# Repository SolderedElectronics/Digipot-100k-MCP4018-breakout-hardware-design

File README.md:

# Digipot 100k MCP4018 breakout Hardware Design

## About the Product

|  |
| :----------------------------------------------------------: |
| [Buy Digipot 100k MCP4018 breakout](https://www.solde.red/333093) |

A digital potentiometer is a device identical to a potentiometer, except that instead of a physical rotating part that adjusts the resistance, it uses digital communication. Namely, the resistance of the digital potentiometer is adjusted via I2C communication.

Our module is based on the MCP4018 IC which has a total of 128 steps between 0 and 100k resistance values. This would mean that it is capable of doing resistance steps of approximately 781 ohms. It is controlled via I2C which makes it extremely easy to use.

---

## Repository Contents

This repository contains all design files for Digipot 100k MCP4018 breakout, organized as follows:

- **`CAD` folder**: Contains KiCAD design files, including:
  - Schematics
  - PCB layout
  - Panel PCB layout
  - Source 3D files in Fusion360, if any
  - All files are sorted by version with a detailed change log.
- **`OUTPUTS` folder**: Includes all production-ready files, such as:
  - Bill of Materials (BOM) and interactive BOM (iBOM)
  - PDF versions of schematics
  - 3D `.step` file of the board
  - 3D-printable models
  - Gerber files for PCB manufacturing
  - Image of the pinout of the board
  - Product image
  - Compliance, legal and generic sales documents

Refer to the `Change Log` in the CAD folder for details about updates between versions.

---

## Learn More About the Product

Beyond the repository, explore the following resources:

### Soldered Verify

The **Soldered Verify** system ensures every board you purchase from Soldered is fully functional. It also provides access to exclusive test data for your product. To get started, find the unique Soldered Verify ID on your product's packaging and enter the ID on the [Soldered Verify page](https://soldered.com/verify/) to access test results and additional product details.

### Soldered Community

Soldered Community is your go-to place for technical support. Our engineers track and answer all questions posted there, and it’s a great space for the maker community. Get answers to your questions and solutions for your challenges at [Soldered Community](https://soldered.com/community).

### solde.red

solde.red is an ultimate URL shortener and information hub. Access it by typing solde.red/ followed by your product SKU, e.g., [solde.red/333000](https://solde.red/333000), to find getting-started guides, datasheets, open-source hardware and software files, certifications, images, pinouts, and more. Read more about the shortener [here](https://solde.red/info/).

---

## Contributing

Contributions are welcome! Here’s how you can get involved:

- Submit pull requests to enhance the design or fix issues.
- Report bugs or problems by opening an issue.

We encourage community collaboration to make this product even better.

---

## About Soldered

[Soldered for Makers](https://soldered.com) specializes in designing and manufacturing electronic products tailored for enthusiasts, ranging from hobbyists to professionals. Our portfolio includes electronic boards, sensors, and actuators that are widely utilized in fields such as microelectronics, mechatronics, robotics, programming, and IoT. Every product we offer is designed in-house and built upon open-source hardware and software platforms. Proudly certified and manufactured within the European Union, our catalog likely includes the product you need for your project.

We complement these products with comprehensive tutorials and manuals, product descriptions, schematics, programming codes, and project examples. Our round-the-clock [customer and technical support](https://soldered.com/community) is available for all our products, irrespective of the sales channel. Soldered’s success and services reflect our maker community’s unwavering [trust](https://www.trustpilot.com/review/soldered.com), for which we are deeply grateful. Join our community and create using Soldered products.

---

## License

All Soldered open-source hardware (OSH) is under The TAPR Open Hardware License. Read more in the LICENSE file located in this repository.

**Disclaimer:**

No warranty - all designs in this repository are distributed in the hope that they will be useful, but without any warranty. They are provided "AS IS", therefore without warranty of any kind, either expressed or implied. The entire quality and performance of what you do with the contents of this repository are your responsibility. In no event Soldered Electronics will be liable for your damages, or losses, including any general, special, incidental, or consequential damage arising out of the use or inability to use the contents of this repository. 

---

## Have fun!

Thank you for your support from your fellow makers at Soldered Electronics.

Happy Making!

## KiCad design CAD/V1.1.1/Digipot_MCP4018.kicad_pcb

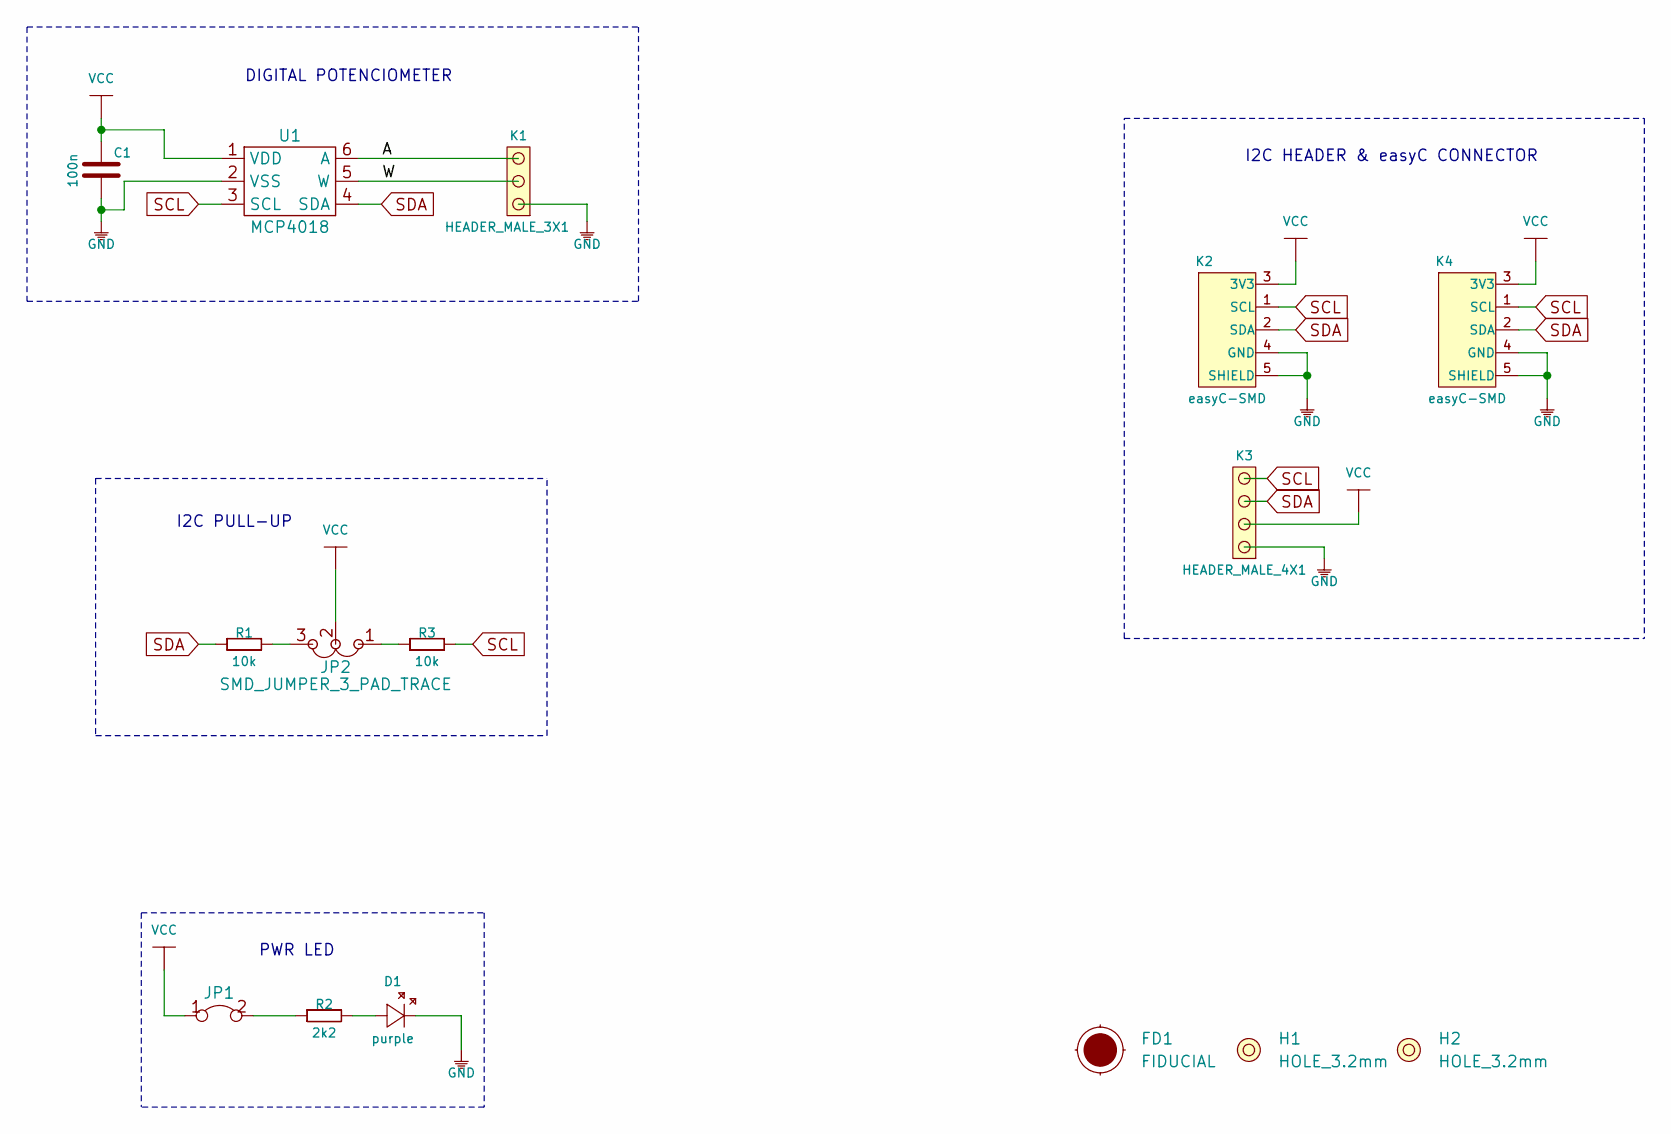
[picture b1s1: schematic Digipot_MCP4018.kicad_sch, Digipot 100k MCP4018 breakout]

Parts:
C1: 100n; 0603C
D1: purple; 0402LED
FD1: FIDUCIAL; FIDUCIAL_23
H1, H2: HOLE_3.2mm
JP1: SMD-JUMPER-CONNECTED_TRACE_SLODERMASK
JP2: SMD_JUMPER_3_PAD_TRACE
K1: HEADER_MALE_3X1
K2, K4: easyC-SMD; easyC-connector
K3: HEADER_MALE_4X1
R1, R3: 10k; 0603R
R2: 2k2; 0402R
U1: MCP4018; SC70-6

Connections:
/A: K1.3, U1.6 (A)
/W: K1.2, U1.5 (W)
GND: C1.1, D1.2 (K), K1.1, K2.4 (GND), K2.5 (SHIELD), K3.1, K4.4 (GND), K4.5 (SHIELD), U1.2 (VSS)
unnamed: D1.1 (A), R2.2
unnamed: JP1.2, R2.1
unnamed: JP2.1, R3.1
unnamed: JP2.3, R1.2
SCL: K2.1 (SCL), K3.4, K4.1 (SCL), R3.2, U1.3 (SCL)
SDA: K2.2 (SDA), K3.3, K4.2 (SDA), R1.1, U1.4 (SDA)
VCC: C1.2, JP1.1, JP2.2, K2.3 (3V3), K3.2, K4.3 (3V3), U1.1 (VDD)

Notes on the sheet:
I2C PULL-UP
I2C HEADER & easyC CONNECTOR
PWR LED
DIGITAL POTENCIOMETER

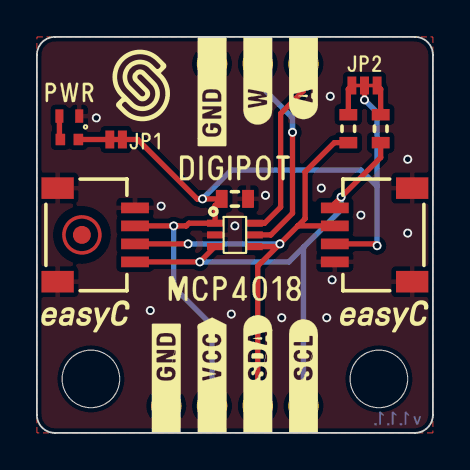
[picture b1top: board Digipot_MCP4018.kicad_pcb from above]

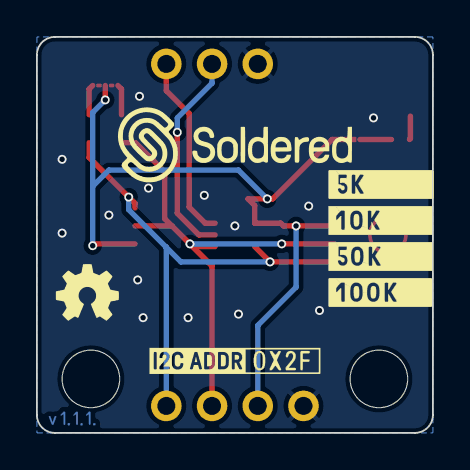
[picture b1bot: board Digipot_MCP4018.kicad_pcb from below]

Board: 2 copper layers, 22.0 x 22.0 mm, 15 parts (2 on the bottom side), 10 nets.

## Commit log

2022-08-06 Updating open source files.
